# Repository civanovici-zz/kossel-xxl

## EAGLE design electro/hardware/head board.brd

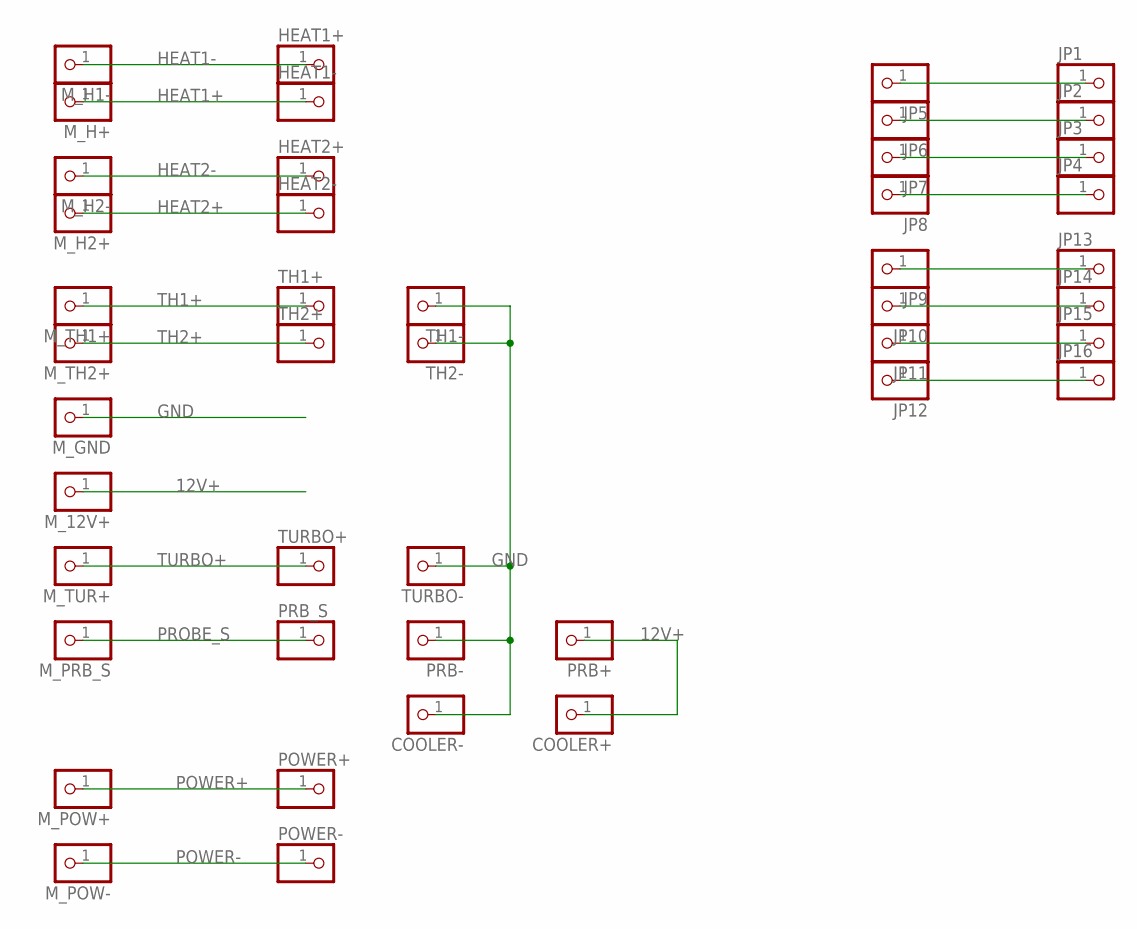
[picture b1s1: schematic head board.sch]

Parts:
COOLER+: PINHD-1X1; 1X01
COOLER-: PINHD-1X1; 1X01
HEAT1+, HEAT1-, HEAT2+, HEAT2-: PINHD-1X1; 1X01
JP1, JP2, JP3, JP4, JP5, JP6, JP7, JP8, JP9, JP10, JP11, JP12, JP13, JP14, JP15, JP16: PINHD-1X1; 1X01
M_12V+: PINHD-1X1; 1X01
M_GND: PINHD-1X1; 1X01
M_H1-, M_H2+, M_H2-: PINHD-1X1; 1X01
M_H+: PINHD-1X1; 1X01
M_POW+: PINHD-1X1; 1X01
M_POW-: PINHD-1X1; 1X01
M_PRB_S: PINHD-1X1; 1X01
M_TH1+, M_TH2+: PINHD-1X1; 1X01
M_TUR+: PINHD-1X1; 1X01
POWER+: PINHD-1X1; 1X01
POWER-: PINHD-1X1; 1X01
PRB+: PINHD-1X1; 1X01
PRB-: PINHD-1X1; 1X01
PRB_S: PINHD-1X1; 1X01
TH1+, TH1-, TH2+, TH2-: PINHD-1X1; 1X01
TURBO+: PINHD-1X1; 1X01
TURBO-: PINHD-1X1; 1X01

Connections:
12V+: COOLER+.1, M_12V+.1, PRB+.1
GND: COOLER-.1, M_GND.1, PRB-.1, TH1-.1, TH2-.1, TURBO-.1
HEAT1+: HEAT1-.1, M_H+.1
HEAT1-: HEAT1+.1, M_H1-.1
HEAT2+: HEAT2-.1, M_H2+.1
HEAT2-: HEAT2+.1, M_H2-.1
unnamed: JP1.1, JP5.1
unnamed: JP2.1, JP6.1
unnamed: JP3.1, JP7.1
unnamed: JP4.1, JP8.1
unnamed: JP9.1, JP13.1
unnamed: JP10.1, JP14.1
unnamed: JP11.1, JP15.1
unnamed: JP12.1, JP16.1
POWER+: M_POW+.1, POWER+.1
POWER-: M_POW-.1, POWER-.1
PROBE_S: M_PRB_S.1, PRB_S.1
TH1+: M_TH1+.1, TH1+.1
TH2+: M_TH2+.1, TH2+.1
TURBO+: M_TUR+.1, TURBO+.1

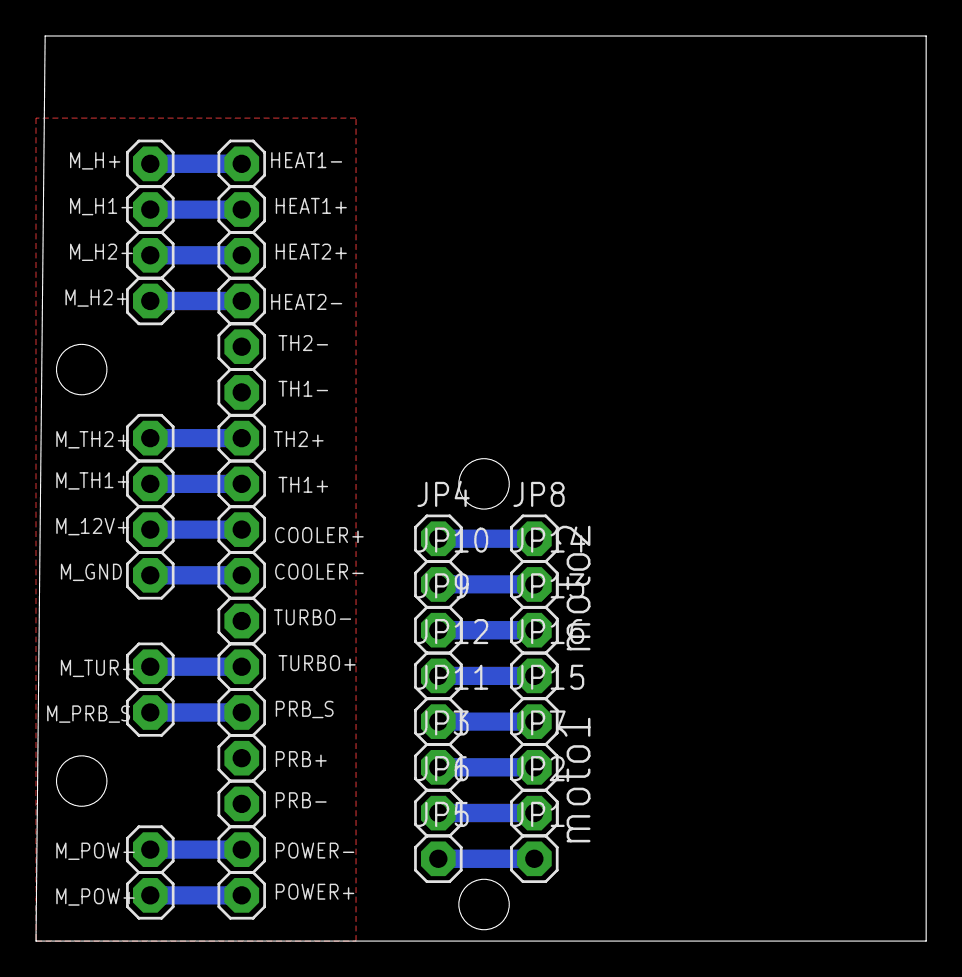
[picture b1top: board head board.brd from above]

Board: 2 copper layers, 49.5 x 50.3 mm, 45 parts (0 on the bottom side), 20 nets.

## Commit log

2016-05-09 more design ready
